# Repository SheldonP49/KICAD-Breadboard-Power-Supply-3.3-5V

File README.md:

Breadboard power supply providing a 3.3V and 5V output, this is the 2nd project 
in Kicad desin course.
There is one vesion for through hole plated board and one for non through hole plated boards.

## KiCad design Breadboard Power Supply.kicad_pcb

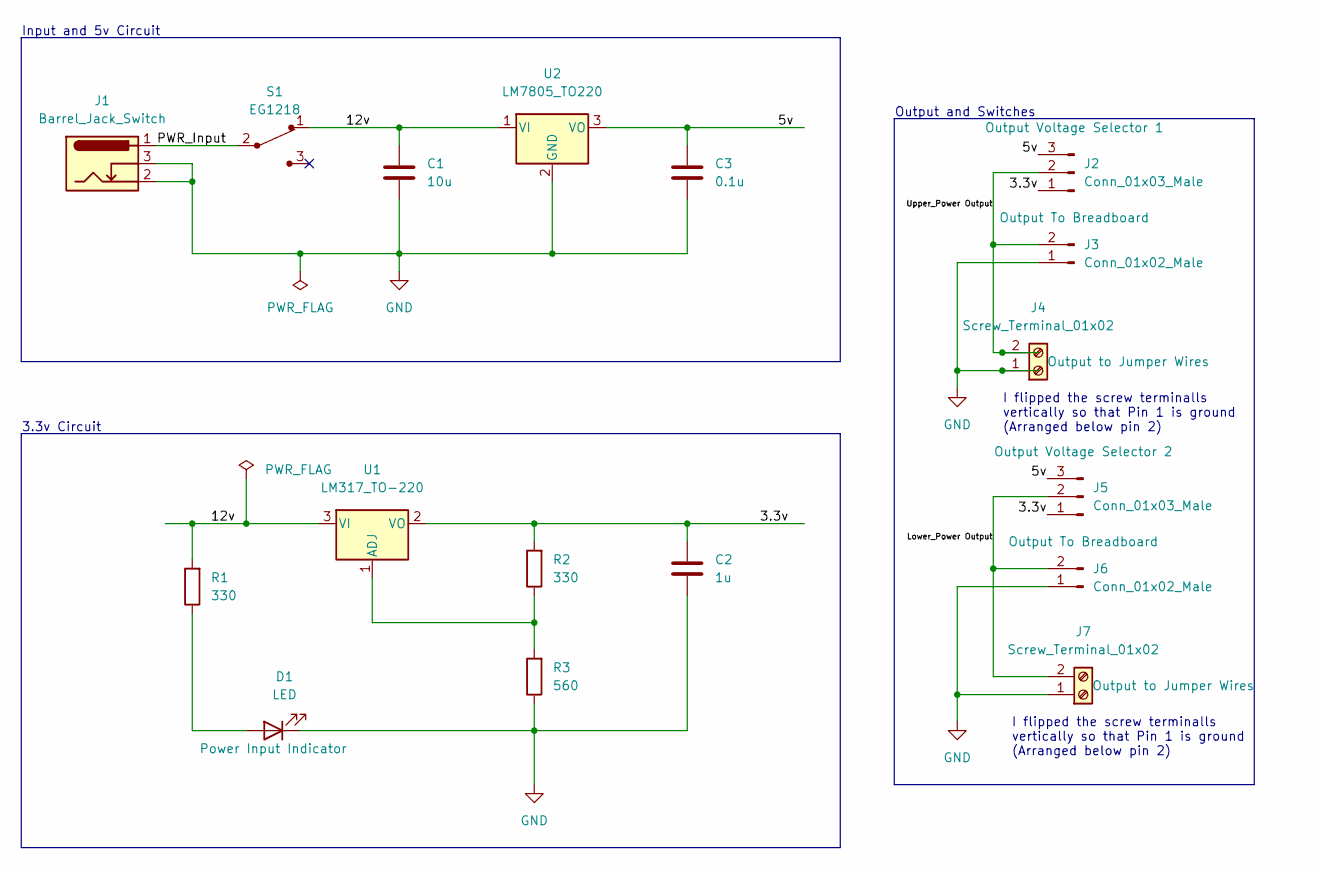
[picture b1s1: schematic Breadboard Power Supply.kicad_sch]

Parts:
C1: 10u; C_Disc_D3.0mm_W1.6mm_P2.50mm
C2: 1u; C_Disc_D3.0mm_W1.6mm_P2.50mm
C3: 0.1u; C_Disc_D3.0mm_W1.6mm_P2.50mm
D1: LED; LED_D5.0mm
J1: Barrel_Jack_Switch; BarrelJack_Horizontal
J2, J5: Conn_01x03_Male; PinHeader_1x03_P2.54mm_Vertical
J3, J6: Conn_01x02_Male; PinHeader_1x02_P2.54mm_Vertical
J4, J7: Screw_Terminal_01x02; TerminalBlock_bornier-2_P5.08mm
R1, R2: 330; R_Axial_DIN0204_L3.6mm_D1.6mm_P7.62mm_Horizontal
R3: 560; R_Axial_DIN0204_L3.6mm_D1.6mm_P7.62mm_Horizontal
S1: EG1218; Switch_Slide_11.6x4mm_EG1218; MPN EG1218; Digi-Key_PN EG1903-ND
U1: LM317_TO-220; TO-220-3_Vertical
U2: LM7805_TO220; TO-220-3_Vertical

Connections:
/3.3v: C2.1, J2.1, J5.1, R2.2, U1.2 (VO)
/5v: C3.1, J2.3, J5.3, U2.3 (VO)
/12v: C1.1, R1.2, S1.1, U1.3 (VI), U2.1 (VI)
/Lower_Power Output: J5.2, J6.2, J7.2
/PWR_Input: J1.1, S1.2
/Upper_Power Output: J2.2, J3.2, J4.2
GND: C1.2, C2.2, C3.2, D1.1 (K), J1.2, J1.3, J3.1, J4.1, J6.1, J7.1, R3.1, U2.2 (GND)
unnamed: D1.2 (A), R1.1
unnamed: R2.1, R3.2, U1.1 (ADJ)

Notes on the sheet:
Input and 5v Circuit
I flipped the screw terminalls vertically so that Pin 1 is ground (Arranged below pin 2)
Output and Switches
3.3v Circuit

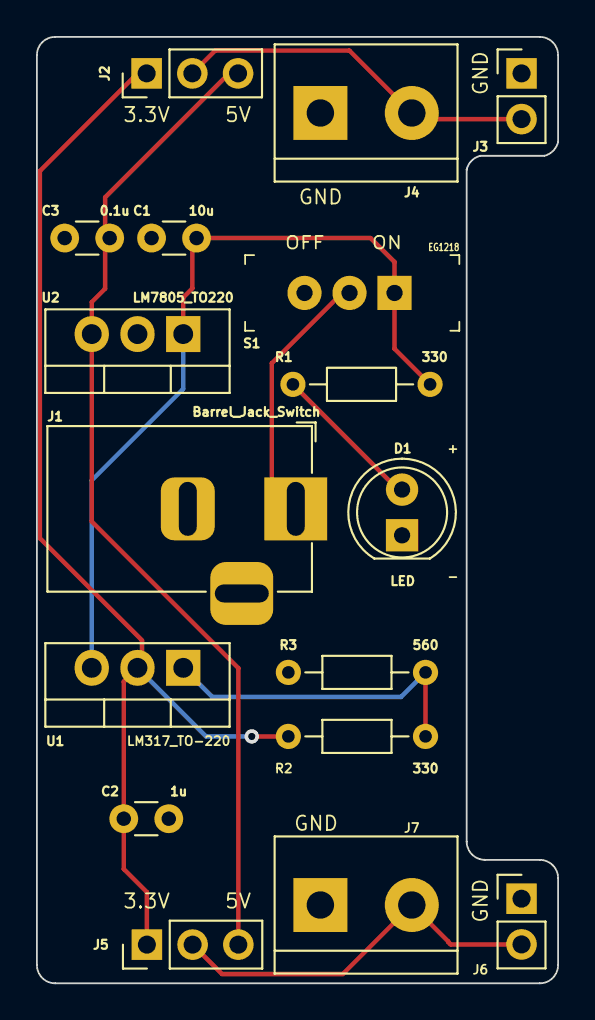
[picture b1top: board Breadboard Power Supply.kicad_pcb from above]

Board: 2 copper layers, 29.0 x 52.6 mm, 17 parts (0 on the bottom side), 9 nets.

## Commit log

2023-02-05 initial commit, adapted version for non through plated hole boards
2023-02-05 reversed tracks for through hole plated version
2023-02-06 additional ignored gerber files
2023-02-06 Ignored erber files for through hole plated version
2023-02-06 Added ignore for through hole version gebers
